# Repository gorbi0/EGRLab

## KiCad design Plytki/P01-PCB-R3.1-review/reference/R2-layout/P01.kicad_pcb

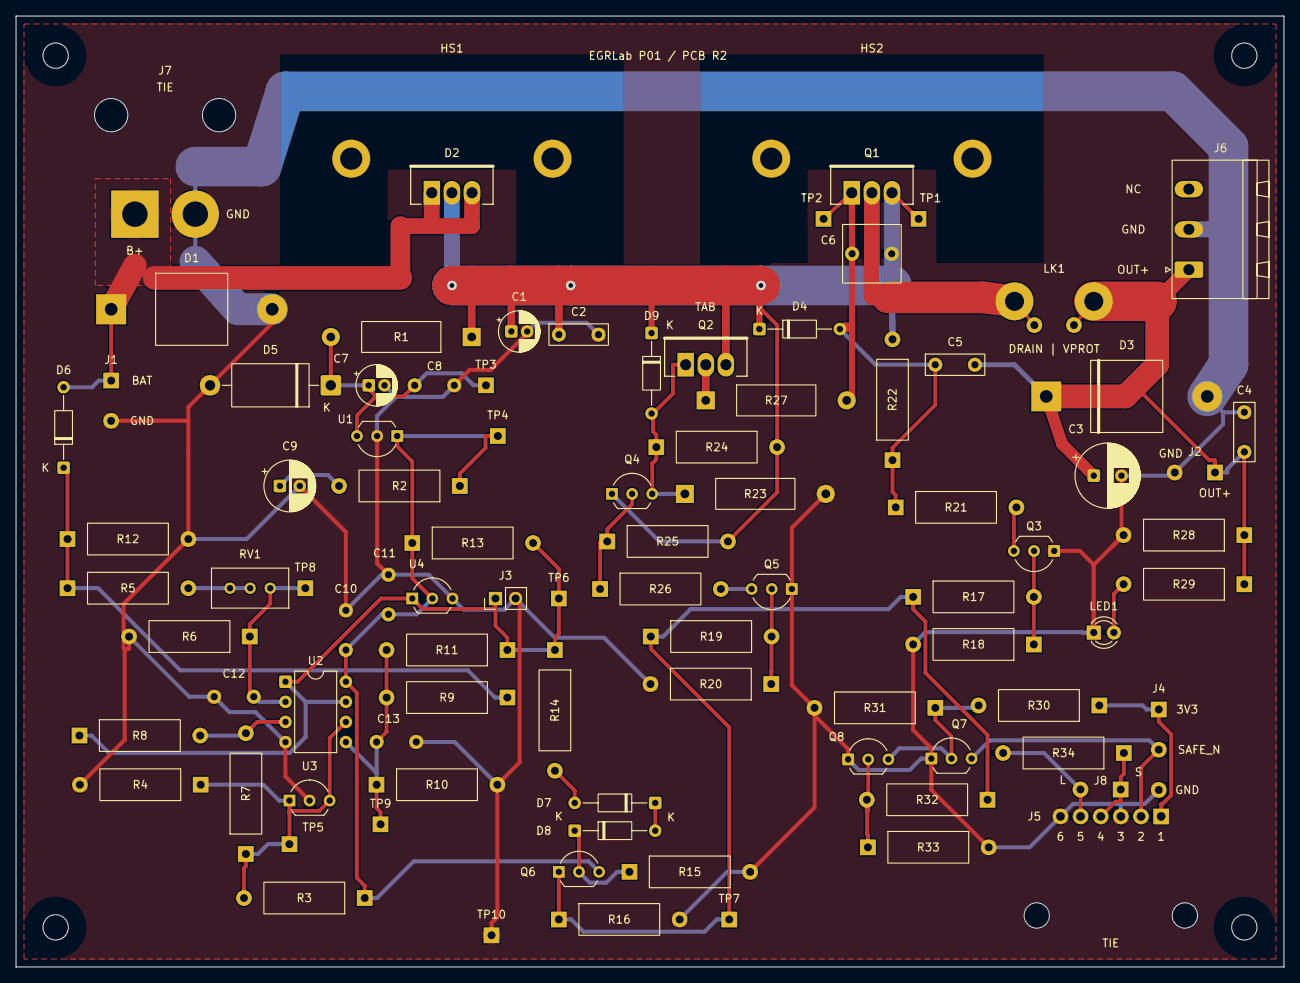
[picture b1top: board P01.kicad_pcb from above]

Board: 2 copper layers, 160.0 x 120.0 mm, 95 parts (0 on the bottom side), 34 nets.

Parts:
C1: 10u / 63V; CP_Radial_D5.0mm_P2.00mm
C2, C4: 100nF / 100V; C_TDK_B32529_L7.3_W2.5_P5
C3: 100u / 50V; CP_Radial_D8.0mm_P3.50mm
C5: 10nF / 100V; C_TDK_B32529_L7.3_W2.5_P5
C6: 1000nF / 100V; C_WIMA_MKS2_1u100V_L7.2_W7.2_P5
C7: 22u / 50V; CP_Radial_D5.0mm_P2.00mm
C8, C10, C11: 100nF / X7R; C_Vishay_K15_H5_P5
C9: 47u / 50V; CP_Radial_D6.3mm_P2.50mm
C12: 100pF / C0G; C_Vishay_K15_H5_P5
C13: 1nF / C0G; C_Vishay_K15_H5_P5
D1: 15KPA24CA; TVS_P600_BIDIR_P20.32
D2: STPS20100CT; TO220_3_P2.54_Drill1.4
D3: 5KP18A; TVS_P600_P20.32
D4: BZX55C15; D_DO-35_SOD27_P10.16mm_Horizontal
D5: 1.5KE18A-E3/54; D_DO-201_P15.24mm_Horizontal
D6, D7, D8: 1N4148; D_DO-35_SOD27_P10.16mm_Horizontal
D9: BZX55C15-TAP; D_DO-35_SOD27_P10.16mm_Horizontal
H1, H2, H3, H4: M3 NPTH
HS1, HS2: SK129-63STS; HS_Fischer_SK129_63.5_STS_D2.8
J1, J2, J8: TEST PADS; TestPads_2
J3: INHIBIT / SHORT=OFF; PinHeader_1x02_P2.54mm_Vertical
J4: TEST PADS; TestPads_3
J5: PG / soldered harness; Pigtail_PG_6xAWG22
J6: SUPPLY / MSTBA 3p; PhoenixContact_MSTBA_2,5_3-G-5,08_1x03_P5.08mm_Horizontal
J7: BAT / soldered wires; Pigtail_PWR_2x2.5mm2
LED1: GREEN 3mm; LED_D3.0mm
LK1: LINK / Cu 2.5mm2; Link_Kelvin_P10
Q1, Q2: SUP53P06-20-E3; TO220_3_P2.54_Drill1.4
Q3, Q5, Q6, Q7, Q8: 2N5551G; TO-92_Inline_Wide
Q4: 2N5401YBU; TO-92_Inline_Wide
R1: 150R / 2W; R_PR02_P17.78
R2: 1R / 0.5W; R_MFR50_H4_P15.24
R3: 820R / 0.5W; R_MFR50_H4_P15.24
R4, R16, R26, R30, R32: 10K / 0.5W; R_MFR50_H4_P15.24
R5: 54K9 / 0.1%; R_MFR50_H4_P15.24
R6, R7, R10: 10K / 0.1%; R_MFR50_H4_P15.24
R8: 220K / 0.1%; R_MFR50_H4_P15.24
R9: 26K1 / 0.1%; R_MFR50_H4_P15.24
R11: 249K / 0.1%; R_MFR50_H4_P15.24
R12, R15, R21, R24, R31: 100K / 0.5W; R_MFR50_H4_P15.24
R13: 2K2 / 0.5W; R_MFR50_H4_P15.24
R14, R17, R19, R28: 4K7 / 0.5W; R_MFR50_H4_P15.24
R18, R20, R25, R33: 47K / 0.5W; R_MFR50_H4_P15.24
R22: 470K / 0.5W; R_MFR50_H4_P15.24
R23: 2K2 / 2W; R_PR02_P17.78
R27: 10R / 2W; R_PR02_P17.78
R29: 6K8 / 0.5W; R_MFR50_H4_P15.24
R34: 0R / link; R_MFR50_H4_P15.24
RV1: 5K / 3296W; Potentiometer_Bourns_3296W_Vertical
TP1: VS; TestPad_1
TP2: GATE; TestPad_1
TP3: AUX_IN; TestPad_1
TP4: AUX5; TestPad_1
TP5: REF; TestPad_1
TP6: OK; TestPad_1
TP7: ENABLE; TestPad_1
TP8: OV_SENSE; TestPad_1
TP9: UV_SENSE; TestPad_1
TP10: GND; TestPad_1
U1: LM2936Z-5.0; TO-92_Inline_Wide
U2: LM2903P; DIP-8_W7.62mm
U3: TL431BILP; TO-92_Inline_Wide
U4: MCP120-450DI/TO; TO-92_Inline_Wide

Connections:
/AUX/P01_AUX_IN: C7.1, C8.1, D5.1, R1.2, TP3.1, U1.3
/AUX/P01_C_AUX_TOP: C9.1, R2.2
/AUX/P01_OV_REF: R7.2, R8.2, U2.3
/AUX/P01_OV_SENSE: C12.1, R6.1, RV1.3, TP8.1, U2.2
/AUX/P01_OV_TRIM_TOP: R5.2, RV1.1, RV1.2
/AUX/P01_REF: R3.2, R4.1, R7.1, TP5.1, U2.6, U3.1, U3.3
/AUX/P01_SENSE_RAW: D6.1, R5.1, R9.1, R12.1
/AUX/P01_UV_SENSE: C13.1, R9.2, R10.1, R11.2, TP9.1, U2.5
/P01_GATE: C5.1, C6.1, D4.2, Q1.1, R21.1, R22.1, R27.2, TP2.1
/P01_LED_A: LED1.2, R29.2
/P01_OFF_BASE: D9.2, Q2.1, Q4.3, R23.1, R24.1
/P01_OFF_COL: Q2.2, R27.1
/P01_ON_BASE: Q3.2, R17.2, R18.1
/P01_ON_COL: Q3.3, R21.2
/P01_Q1_DRAIN: LK1.1, Q1.2
/P01_RELEASE_BASE: Q5.2, R19.2, R20.1
/P01_RELEASE_COL: Q5.3, R26.2
/P01_RELEASE_PBASE: Q4.2, R25.1, R26.1
/SAFE/3V3_IO: J4.1, J5.1, R30.1
/SAFE/P01_BUF_BASE: D8.1, Q6.2, R15.1
/SAFE/P01_BUF_D1: D7.2, R14.2
/SAFE/P01_BUF_D2: D7.1, D8.2
/SAFE/P01_FAULT_BASE: Q7.2, Q8.3, R30.2, R31.1
/SAFE/P01_FAULT_RELEASE_BASE: Q8.2, R32.2, R33.1
/SAFE/PG_LINK: J5.5, J8.2, R34.2
/SAFE/PG_SEND: J5.4, J8.1, R34.1
/SAFE/SAFE_N: J4.2, J5.2, Q7.3
/VPROT: C3.1, C4.1, C5.2, D3.1, J2.1, J6.1, LK1.2, R28.1, R29.1
BAT_FUSED: D1.1, D2.1, D2.3, D6.2, J1.1, J7.1
GND: C1.2, C2.2, C3.2, C4.2, C7.2, C8.2, C9.2, C10.2, C11.2, C12.2, C13.2, D1.2, D3.2, D5.2, J1.2, J2.2, J3.2, J4.3, J5.3, J5.6, J6.2, J7.2, LED1.1, Q3.1, Q5.1, Q7.1, Q8.1, R4.2, R6.2, R10.2, R12.2, R15.2, R16.2, R18.2, R20.2, R23.2, R28.2, R31.2, R33.2, TP10.1, U1.2, U2.4, U3.2, U4.3
P01_AUX5: C10.1, C11.1, Q6.3, R2.1, R3.1, R13.1, TP4.1, U1.1, U2.8, U4.2
P01_ENABLE: Q6.1, R16.1, R17.1, R19.1, R32.1, TP7.1
P01_OK: J3.1, R8.1, R11.1, R13.2, R14.1, TP6.1, U2.1, U2.7, U4.1
P01_VS: C1.1, C2.1, C6.2, D2.2, D4.1, D9.1, Q1.3, Q2.3, Q4.1, R1.1, R22.2, R24.2, R25.2, TP1.1

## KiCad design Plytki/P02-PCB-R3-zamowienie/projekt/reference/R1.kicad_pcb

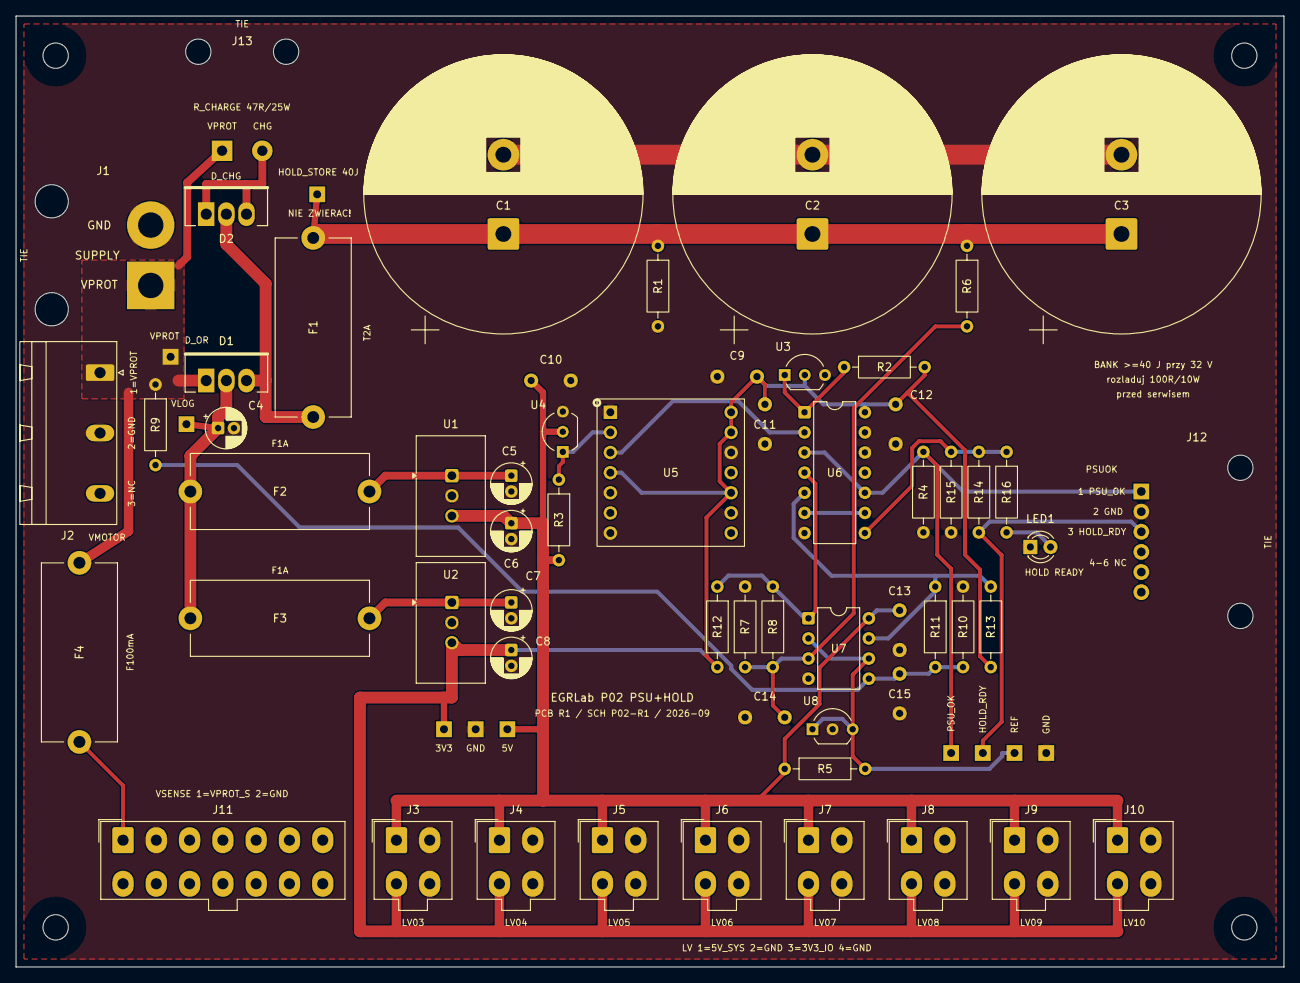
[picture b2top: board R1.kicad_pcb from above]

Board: 2 copper layers, 160.0 x 120.0 mm, 73 parts (0 on the bottom side), 24 nets.

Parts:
C1, C2, C3: 22000u / 35V; CP_Radial_D35.0mm_P10.00mm_SnapIn
C4: 22u / 50V; CP_Radial_D5.0mm_P2.00mm
C5, C7: 10u / 50V; CP_Radial_D5.0mm_P2.00mm
C6, C8: 22u / 16V; CP_Radial_D5.0mm_P2.00mm
C9, C10, C11, C12, C13, C14, C15: 100nF / X7R; C_Vishay_K15_H5_P5
D1: STPS20100CT / D_OR; TO220_3_P2.54_Drill1.4
D2: STPS20100CT / D_CHARGE; TO220_3_P2.54_Drill1.4
F1: T2A / 5x20 DC; Fuseholder_Cylinder-5x20mm_Stelvio-Kontek_PTF78_Horizontal_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
F2, F3: 1A / 5x20; Fuseholder_Cylinder-5x20mm_Stelvio-Kontek_PTF78_Horizontal_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
F4: F100mA / 5x20; Fuseholder_Cylinder-5x20mm_Stelvio-Kontek_PTF78_Horizontal_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
H1, H2, H3, H4: M3 NPTH
J1: SUPPLY / soldered wires; Pigtail_PWR_2x2.5mm2
J2: VMOTOR / GMSTBA 3p 7.62; PhoenixContact_GMSTBA_2,5_3-G-7,62_1x03_P7.62mm_Horizontal
J3: LV03 / Mini-Fit Jr 4p; Molex_Mini-Fit_Jr_5566-04A_2x02_P4.20mm_Vertical
J4: LV04 / Mini-Fit Jr 4p; Molex_Mini-Fit_Jr_5566-04A_2x02_P4.20mm_Vertical
J5: LV05 / Mini-Fit Jr 4p; Molex_Mini-Fit_Jr_5566-04A_2x02_P4.20mm_Vertical
J6: LV06 / Mini-Fit Jr 4p; Molex_Mini-Fit_Jr_5566-04A_2x02_P4.20mm_Vertical
J7: LV07 / Mini-Fit Jr 4p; Molex_Mini-Fit_Jr_5566-04A_2x02_P4.20mm_Vertical
J8: LV08 / Mini-Fit Jr 4p; Molex_Mini-Fit_Jr_5566-04A_2x02_P4.20mm_Vertical
J9: LV09 / Mini-Fit Jr 4p; Molex_Mini-Fit_Jr_5566-04A_2x02_P4.20mm_Vertical
J10: LV10 / Mini-Fit Jr 4p; Molex_Mini-Fit_Jr_5566-04A_2x02_P4.20mm_Vertical
J11: VSENSE / Mini-Fit Jr 14p; Molex_Mini-Fit_Jr_5566-14A_2x07_P4.20mm_Vertical
J12: PSUOK / soldered ribbon; Pigtail_PSUOK_6x_P2.54
J13: R_CHARGE / wires; Pigtail_RCHARGE_2xAWG20
LED1: GREEN 3mm / HOLD READY; LED_D3.0mm
R1: 4K7 / 1%; R_Axial_DIN0207_L6.3mm_D2.5mm_P10.16mm_Horizontal
R2, R3, R4, R12, R13, R15: 10K / 1%; R_Axial_DIN0207_L6.3mm_D2.5mm_P10.16mm_Horizontal
R5, R14, R16: 1K / 1%; R_Axial_DIN0207_L6.3mm_D2.5mm_P10.16mm_Horizontal
R6: 267K / 1%; R_Axial_DIN0207_L6.3mm_D2.5mm_P10.16mm_Horizontal
R7, R10: 100K / 1%; R_Axial_DIN0207_L6.3mm_D2.5mm_P10.16mm_Horizontal
R8, R11: 2M2 / 1%; R_Axial_DIN0207_L6.3mm_D2.5mm_P10.16mm_Horizontal
R9: 348K / 1%; R_Axial_DIN0207_L6.3mm_D2.5mm_P10.16mm_Horizontal
TP1: VPROT; TestPad_1
TP2: VLOG_RES; TestPad_1
TP3: HOLD_STORE; TestPad_1
TP4: 5V_SYS; TestPad_1
TP5: 3V3_IO; TestPad_1
TP6, TP10: GND; TestPad_1
TP7: PSU_OK; TestPad_1
TP8: HOLD_READY; TestPad_1
TP9: REF25; TestPad_1
U1: TSR 2-2450; Converter_DCDC_TRACO_TSR2-xxxx_THT
U2: TSR 2-2433; Converter_DCDC_TRACO_TSR2-xxxx_THT
U3: MCP120-300DI/TO; TO-92_Inline_Wide
U4: MCP120-450DI/TO; TO-92_Inline_Wide
U5: 74LVC125A / SO14 adapter; Adapter_SO14_DIP14_W15.24_Kamami575068
U6: SN74HC08N; DIP-14_W7.62mm
U7: LM2903P; DIP-8_W7.62mm
U8: TL431BILP; TO-92_Inline_Wide

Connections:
3V3_IO: C8.1, C9.1, C11.1, C12.1, J3.3, J4.3, J5.3, J6.3, J7.3, J8.3, J9.3, J10.3, R2.2, R12.2, R13.2, TP5.1, U2.3, U3.2, U5.4, U5.10, U5.13, U5.14, U6.14
5V_SYS: C6.1, C10.1, C13.1, J3.1, J4.1, J5.1, J6.1, J7.1, J8.1, J9.1, J10.1, R3.2, R5.1, TP4.1, U1.3, U4.2, U7.8
/CHARGE_D: D2.1, D2.3, J13.2
/HOLD_FUSED: D1.3, D2.2, F1.1
/MON/HOLD_READY: J12.3, R14.2, TP8.1
/MON/P02_BANK_DIV: C14.1, R6.2, R7.1, R8.2, U7.3
/MON/P02_BANK_OK: R8.1, R12.1, U6.4, U7.1
/MON/P02_HOLD_QUAL: U6.6, U6.9
/MON/P02_HOLD_READY_INT: R14.1, R15.1, R16.1, U6.8
/MON/P02_LED_A: LED1.2, R16.2
/MON/P02_REF25: R5.2, TP9.1, U7.2, U7.6, U8.1, U8.3
/MON/P02_SUP3_N: R2.1, U3.1, U6.1
/MON/P02_SUP5_N: U5.3, U6.2
/MON/P02_SUP5_RAW: R3.1, U4.1, U5.2
/MON/P02_VPROT_DIV: C15.1, R9.2, R10.1, R11.2, U7.5
/MON/P02_VPROT_OK: R11.1, R13.1, U6.5, U7.7
/MON/PSU_OK: J12.1, R4.1, TP7.1, U6.3, U6.10
/P02_VIN_DC5: C5.1, F2.2, U1.1
/P02_VIN_DC33: C7.1, F3.2, U2.1
/VLOG_RES: C4.1, D1.2, F2.1, F3.1, TP2.1
/VPROT_SENSE: F4.2, J11.1
GND: C1.2, C2.2, C3.2, C4.2, C5.2, C6.2, C7.2, C8.2, C9.2, C10.2, C11.2, C12.2, C13.2, C14.2, C15.2, J1.2, J2.2, J3.2, J3.4, J4.2, J4.4, J5.2, J5.4, J6.2, J6.4, J7.2, J7.4, J8.2, J8.4, J9.2, J9.4, J10.2, J10.4, J11.2, J12.2, LED1.1, R1.2, R4.2, R7.2, R10.2, R15.2, TP6.1, TP10.1, U1.2, U2.2, U3.3, U4.3, U5.1, U5.5, U5.7, U5.9, U5.12, U6.7, U6.12, U6.13, U7.4, U8.2
HOLD_STORE: C1.1, C2.1, C3.1, F1.2, R1.1, R6.1, TP3.1
VPROT: D1.1, F4.1, J1.1, J2.1, J13.1, R9.1, TP1.1
